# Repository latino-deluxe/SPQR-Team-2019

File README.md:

# SPQR-Team-2019
Official code 2018-2019 SPQR
1st at Romecup2019, Rome
Best Robot Design at Robocup2019, Sydney

#include <E.Latino>

#include <A.Ghezzi>

#include <E.Coletta>

#include <D.Casagrande>

#include <S.Sannino>

#include <G.Treccape>

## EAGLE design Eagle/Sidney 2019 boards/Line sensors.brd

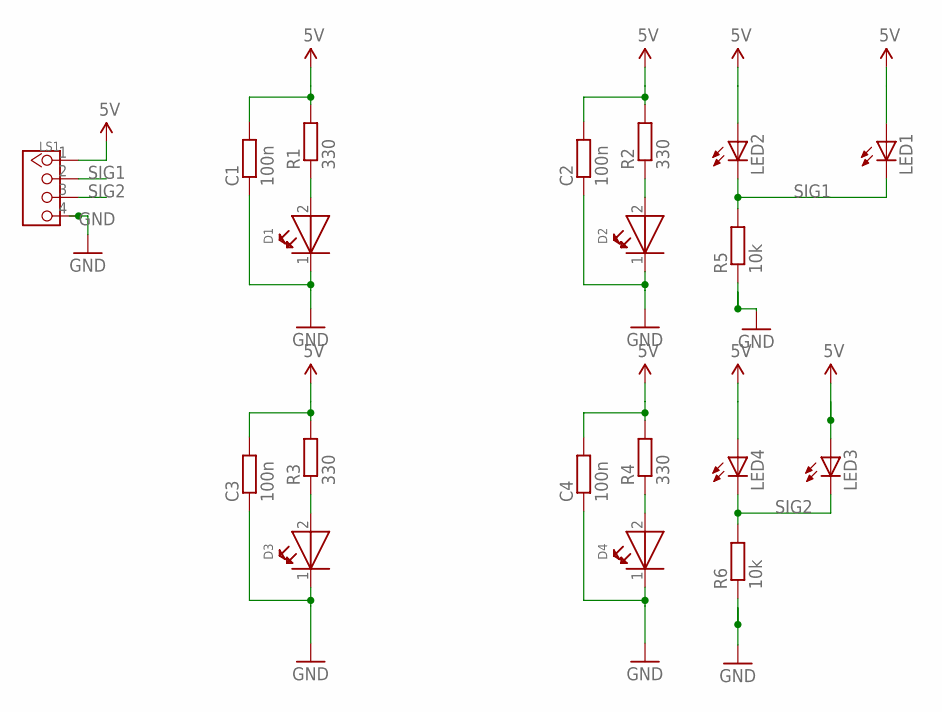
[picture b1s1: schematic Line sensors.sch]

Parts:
C1, C2, C3, C4: 100n; M0805
D1, D2, D3, D4: WL-SMTW-150141AS73100-A; 3528-2PIN
LED1, LED2, LED3, LED4: LED3MM
LS1: TWIG-4P-2.0-2.0; 4P-2.0
R1, R2, R3, R4: 330; M0805
R5, R6: 10k; M0805

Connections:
5V: C1.2, C2.2, C3.2, C4.2, LED1.A, LED2.A, LED3.A, LED4.A, LS1.1, R1.2, R2.2, R3.2, R4.2
GND: C1.1, C2.1, C3.1, C4.1, D1.1 (K), D2.1 (K), D3.1 (K), D4.1 (K), LS1.4, R5.1, R6.1
unnamed: D1.2 (A), R1.1
unnamed: D2.2 (A), R2.1
unnamed: D3.2 (A), R3.1
unnamed: D4.2 (A), R4.1
SIG1: LED1.K (C), LED2.K (C), LS1.2, R5.2
SIG2: LED3.K (C), LED4.K (C), LS1.3, R6.2

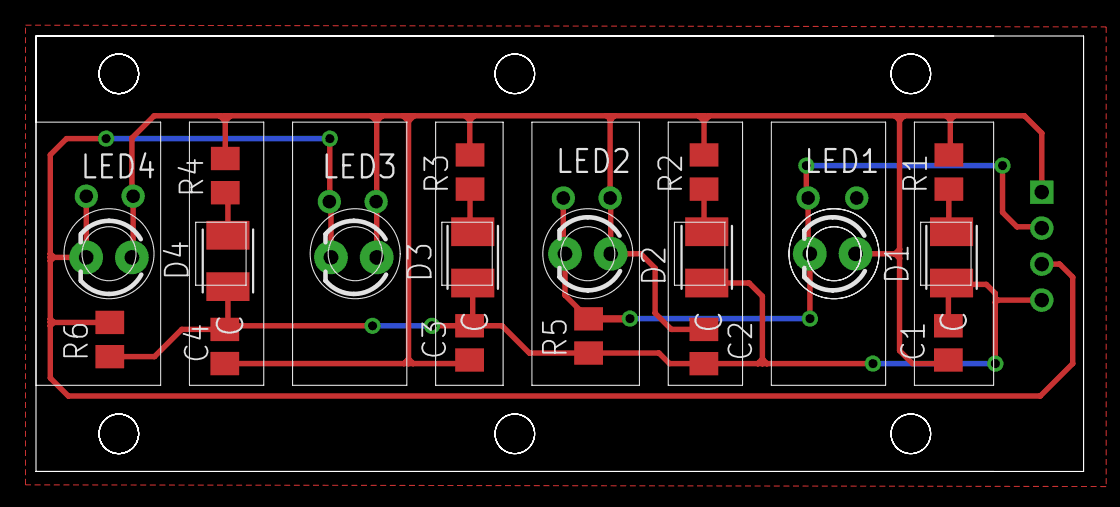
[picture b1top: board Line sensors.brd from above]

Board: 2 copper layers, 58.2 x 24.2 mm, 19 parts (1 on the bottom side), 8 nets.

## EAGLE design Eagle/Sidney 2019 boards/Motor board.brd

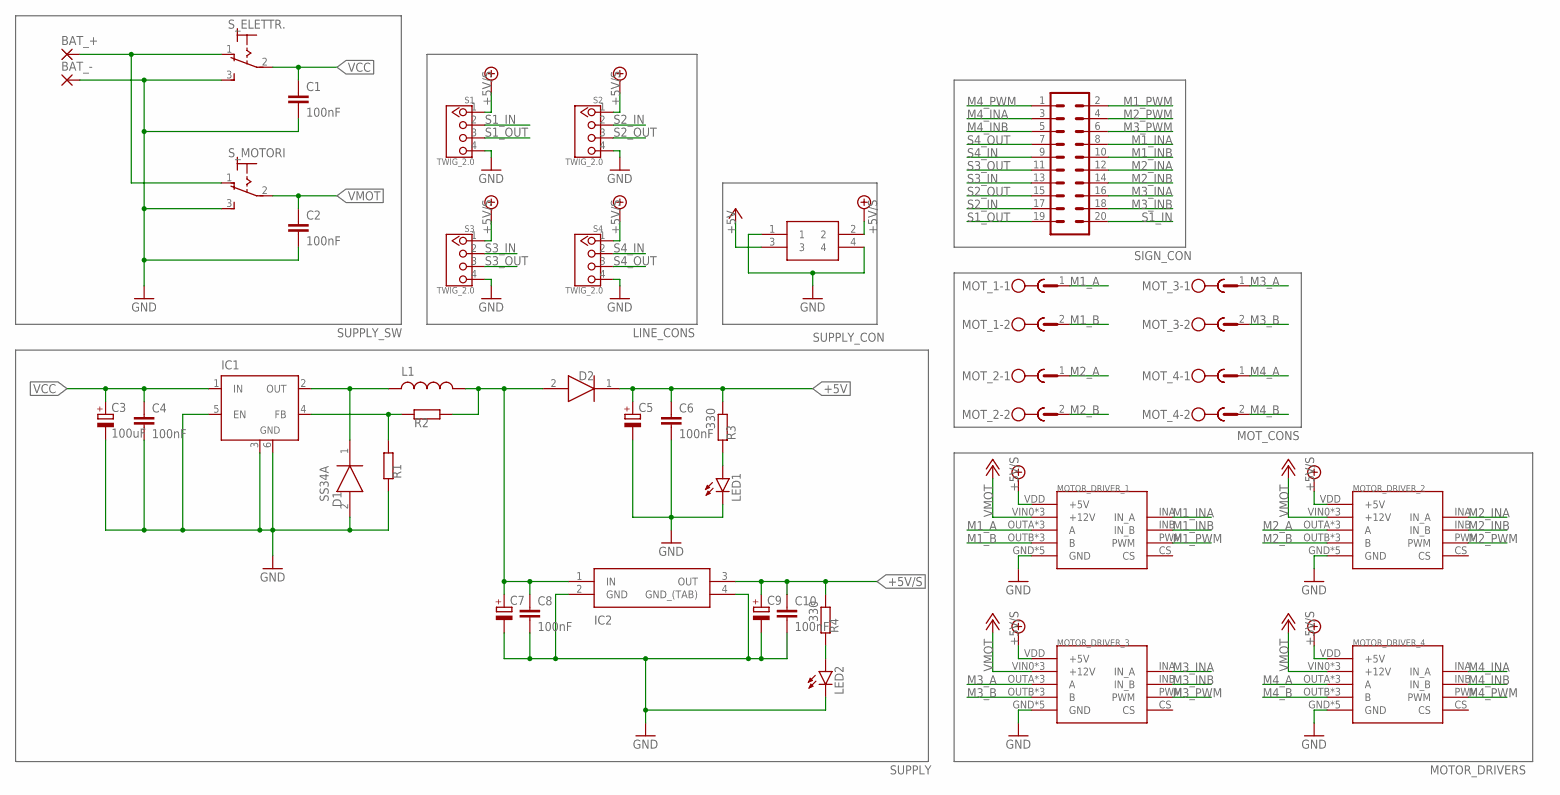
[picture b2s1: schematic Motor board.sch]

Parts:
BAT_+: 3,81/1,4
BAT_-: 3,81/1,4
C1, C2, C4, C6, C8, C10: 100nF; C1206
C3: 100uF; CT7343
C5, C7, C9: CPOL-EUE; PANASONIC_E
D1: SS34A; DIOM5026X262N
D2: SE20FG-M3_H; SODFL3718X108N
IC1: LM2596S; TO263-5
IC2: LM2940CS-5.0_NOPB; TO254P1435X464-4N
L1: 47uH; MSS1260
LED1, LED2: LEDSML1206; SML1206
MOTOR_DRIVER_1, MOTOR_DRIVER_2, MOTOR_DRIVER_3, MOTOR_DRIVER_4: VNH5019
MOT_1, MOT_2, MOT_3, MOT_4: MST2V; MSTBV2
R1, R3, R4: 330; R1206
R2: 1,2k; R1206
S1, S2, S3, S4: TWIG_2.0; 2.0_1X4
SIGN_CON: 20V
SUPPLY_CON: 39-28-1043
S_ELETTR.: 320-916
S_MOTORI: 320-916

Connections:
5.7V-DIRAMAZIONE2: C7.+, C8.1, D2.2 (A), IC2.1 (IN), L1.P$1, R2.1
+5V: C5.+, C6.1, D2.1 (K), R3.1, SUPPLY_CON.3; also elsewhere on the board
GND: BAT_-.1, C1.2, C2.2, C3.-, C4.2, C5.-, C6.2, C7.-, C8.2, C9.-, C10.2, D1.2 (A), IC1.3 (GND), IC1.5 (EN), IC1.6 (GND), IC2.2 (GND), IC2.4 (GND_(TAB)), LED1.C, LED2.C, MOTOR_DRIVER_1.GND, MOTOR_DRIVER_1.GND0 (GND), MOTOR_DRIVER_1.GND1 (GND), MOTOR_DRIVER_1.GND2 (GND), MOTOR_DRIVER_1.GND3 (GND), MOTOR_DRIVER_2.GND, MOTOR_DRIVER_2.GND0 (GND), MOTOR_DRIVER_2.GND1 (GND), MOTOR_DRIVER_2.GND2 (GND), MOTOR_DRIVER_2.GND3 (GND), MOTOR_DRIVER_3.GND, MOTOR_DRIVER_3.GND0 (GND), MOTOR_DRIVER_3.GND1 (GND), MOTOR_DRIVER_3.GND2 (GND), MOTOR_DRIVER_3.GND3 (GND), MOTOR_DRIVER_4.GND, MOTOR_DRIVER_4.GND0 (GND), MOTOR_DRIVER_4.GND1 (GND), MOTOR_DRIVER_4.GND2 (GND), MOTOR_DRIVER_4.GND3 (GND), R1.1, S1.4, S2.4, S3.4, S4.4, SUPPLY_CON.1, SUPPLY_CON.4, S_ELETTR..3 (S), S_MOTORI.3 (S); also elsewhere on the board
M1_A: MOTOR_DRIVER_1.OUTA (A), MOTOR_DRIVER_1.OUTA2 (A), MOTOR_DRIVER_1.OUTA3 (A), MOT_1.1
M1_B: MOTOR_DRIVER_1.OUTB (B), MOTOR_DRIVER_1.OUTB1 (B), MOTOR_DRIVER_1.OUTB3 (B), MOT_1.2
M1_INA: MOTOR_DRIVER_1.INA (IN_A), SIGN_CON.8
M1_INB: MOTOR_DRIVER_1.INB (IN_B), SIGN_CON.10
M1_PWM: MOTOR_DRIVER_1.PWM, SIGN_CON.2
M2_A: MOTOR_DRIVER_2.OUTA (A), MOTOR_DRIVER_2.OUTA2 (A), MOTOR_DRIVER_2.OUTA3 (A), MOT_2.1
M2_B: MOTOR_DRIVER_2.OUTB (B), MOTOR_DRIVER_2.OUTB1 (B), MOTOR_DRIVER_2.OUTB3 (B), MOT_2.2
M2_INA: MOTOR_DRIVER_2.INA (IN_A), SIGN_CON.12
M2_INB: MOTOR_DRIVER_2.INB (IN_B), SIGN_CON.14
M2_PWM: MOTOR_DRIVER_2.PWM, SIGN_CON.4
M3_A: MOTOR_DRIVER_3.OUTA (A), MOTOR_DRIVER_3.OUTA2 (A), MOTOR_DRIVER_3.OUTA3 (A), MOT_3.1
M3_B: MOTOR_DRIVER_3.OUTB (B), MOTOR_DRIVER_3.OUTB1 (B), MOTOR_DRIVER_3.OUTB3 (B), MOT_3.2
M3_INA: MOTOR_DRIVER_3.INA (IN_A), SIGN_CON.16
M3_INB: MOTOR_DRIVER_3.INB (IN_B), SIGN_CON.18
M3_PWM: MOTOR_DRIVER_3.PWM, SIGN_CON.6
M4_A: MOTOR_DRIVER_4.OUTA (A), MOTOR_DRIVER_4.OUTA2 (A), MOTOR_DRIVER_4.OUTA3 (A), MOT_4.1
M4_B: MOTOR_DRIVER_4.OUTB (B), MOTOR_DRIVER_4.OUTB1 (B), MOTOR_DRIVER_4.OUTB3 (B), MOT_4.2
M4_INA: MOTOR_DRIVER_4.INA (IN_A), SIGN_CON.3
M4_INB: MOTOR_DRIVER_4.INB (IN_B), SIGN_CON.5
M4_PWM: MOTOR_DRIVER_4.PWM, SIGN_CON.1
unnamed: BAT_+.1, S_ELETTR..1 (O), S_MOTORI.1 (O)
unnamed: LED2.A, R4.2
unnamed: LED1.A, R3.2
unnamed: D1.1 (K), IC1.2 (OUT), L1.P$2
unnamed: IC1.4 (FB), R1.2, R2.2
S1_IN: S1.2, SIGN_CON.20
S1_OUT: S1.3, SIGN_CON.19
S2_IN: S2.2, SIGN_CON.17
S2_OUT: S2.3, SIGN_CON.15
S3_IN: S3.2, SIGN_CON.13
S3_OUT: S3.3, SIGN_CON.11
S4_IN: S4.2, SIGN_CON.9
S4_OUT: S4.3, SIGN_CON.7
VCC: C1.1, C3.+, C4.1, IC1.1 (IN), S_ELETTR..2
VMOT: C2.1, MOTOR_DRIVER_1.VIN0 (+12V), MOTOR_DRIVER_1.VIN1 (+12V), MOTOR_DRIVER_1.VIN2 (+12V), MOTOR_DRIVER_2.VIN0 (+12V), MOTOR_DRIVER_2.VIN1 (+12V), MOTOR_DRIVER_2.VIN2 (+12V), MOTOR_DRIVER_3.VIN0 (+12V), MOTOR_DRIVER_3.VIN1 (+12V), MOTOR_DRIVER_3.VIN2 (+12V), MOTOR_DRIVER_4.VIN0 (+12V), MOTOR_DRIVER_4.VIN1 (+12V), MOTOR_DRIVER_4.VIN2 (+12V), S_MOTORI.2

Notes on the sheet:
SUPPLY_SW
SUPPLY
LINE_CONS
MOT_CONS
MOTOR_DRIVERS

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
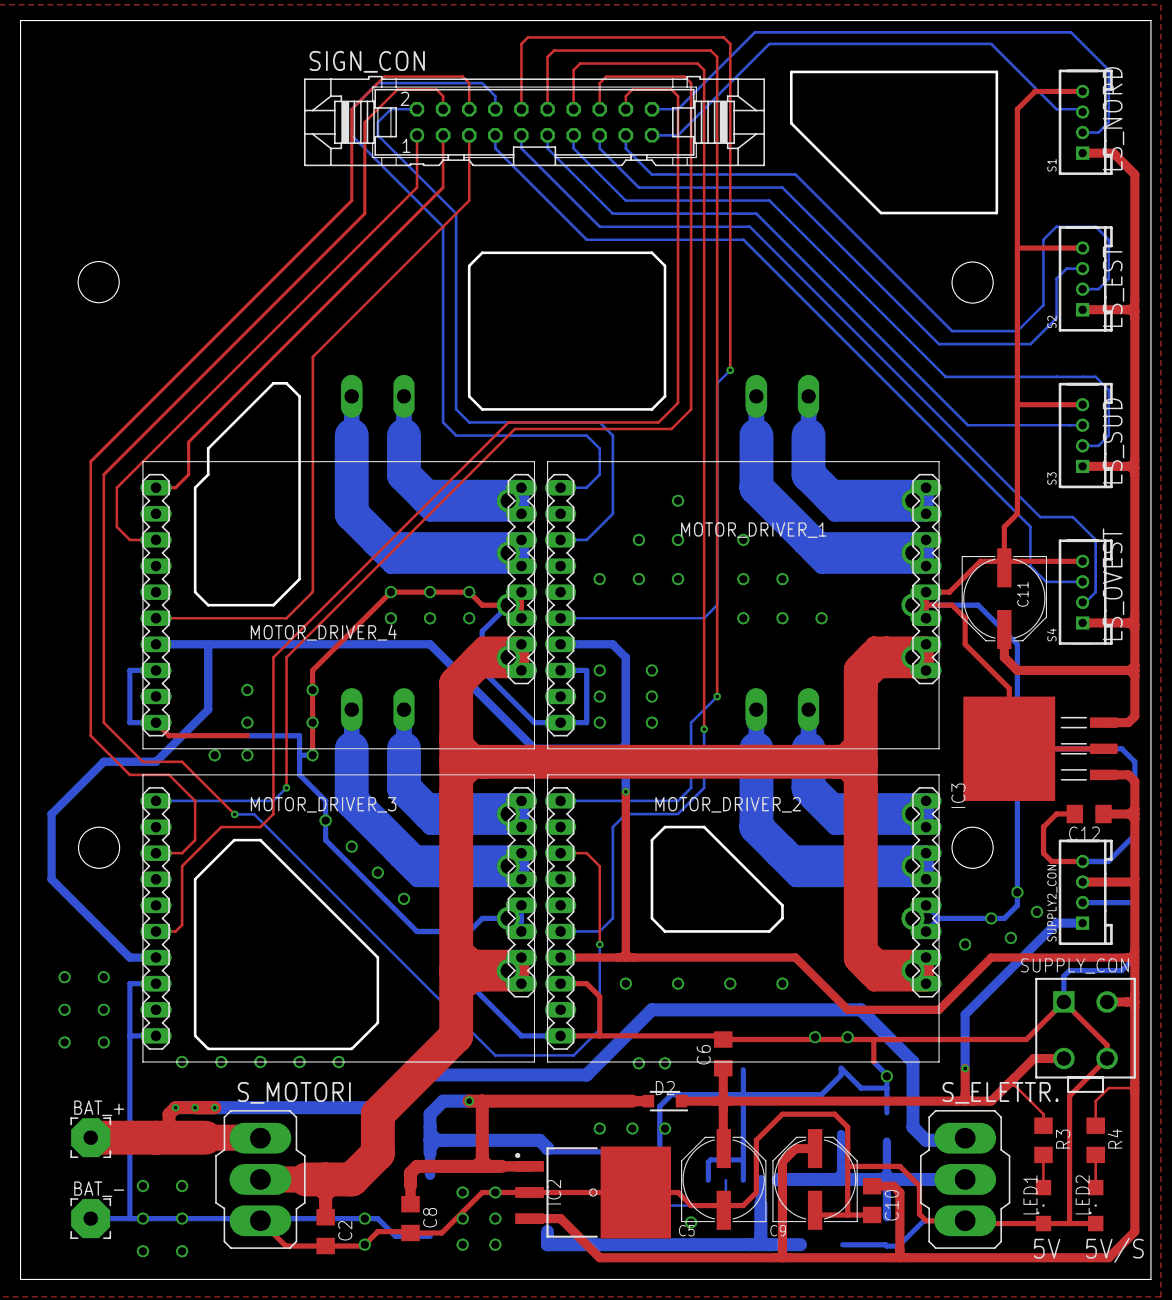
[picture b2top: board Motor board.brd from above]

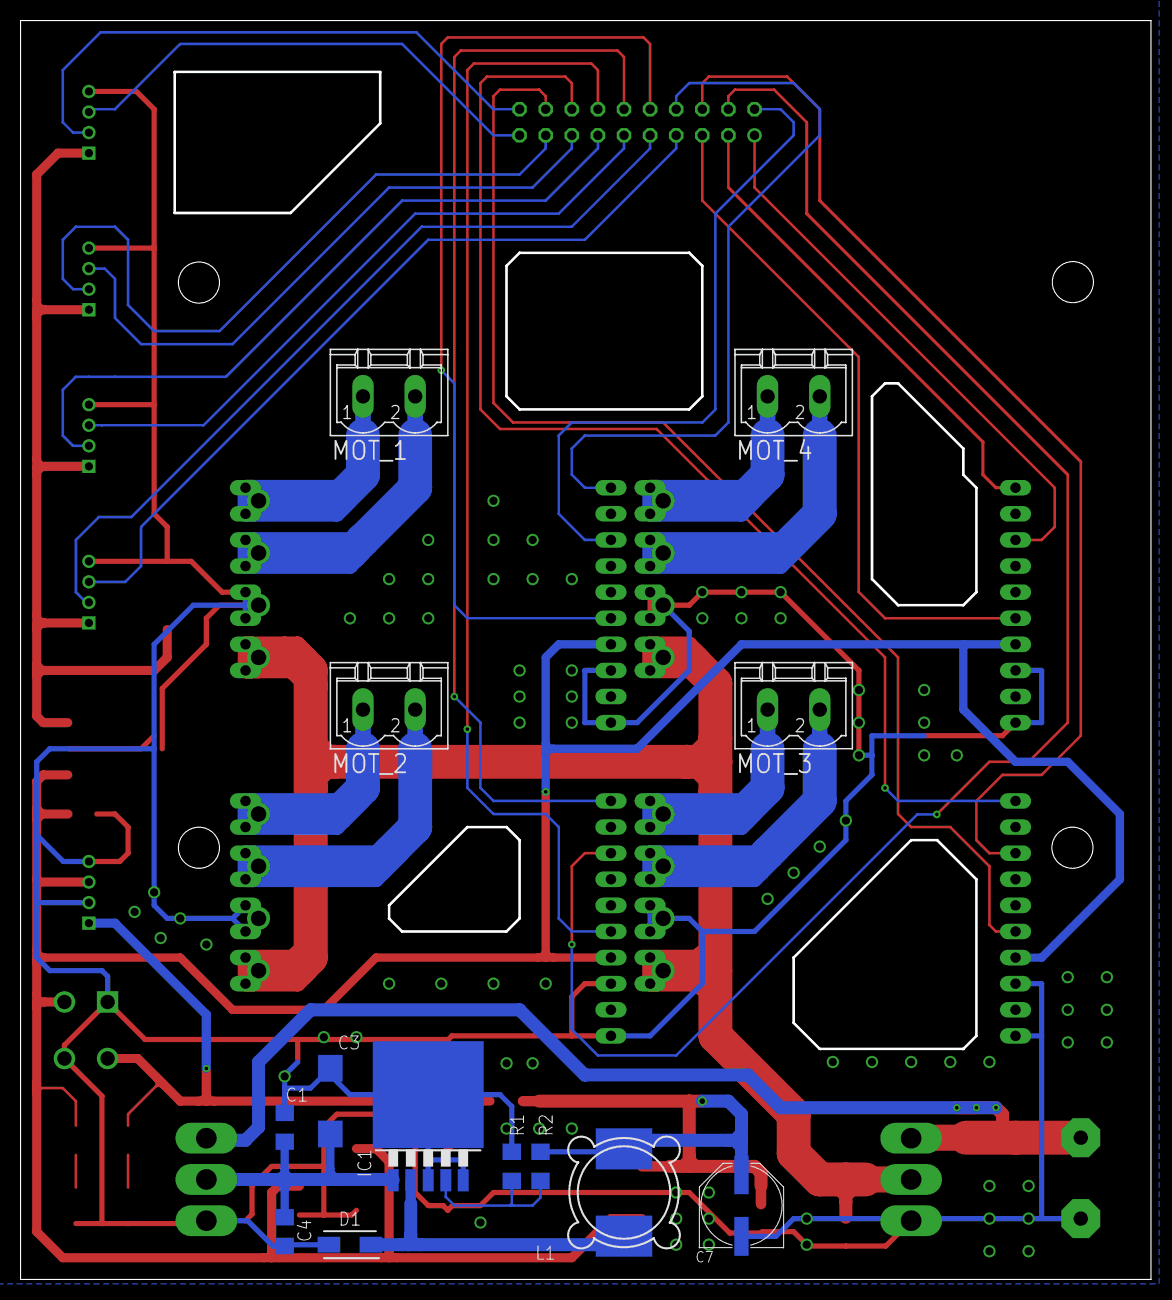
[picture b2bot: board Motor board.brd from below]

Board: 2 copper layers, 110.0 x 122.5 mm, 43 parts (13 on the bottom side), 40 nets.

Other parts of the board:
C11: PANASONIC_E
C12: 100nF; C1206
IC3: LM3940IS-3.3; TO254P1435X457-4N
SUPPLY2_CON: TWIG_2.0; 2.0_1X4

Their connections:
+5V: SUPPLY2_CON.1; also elsewhere on the board
GND: C11.-, C12.2, IC3.2, IC3.4, SUPPLY2_CON.2, SUPPLY2_CON.4; also elsewhere on the board

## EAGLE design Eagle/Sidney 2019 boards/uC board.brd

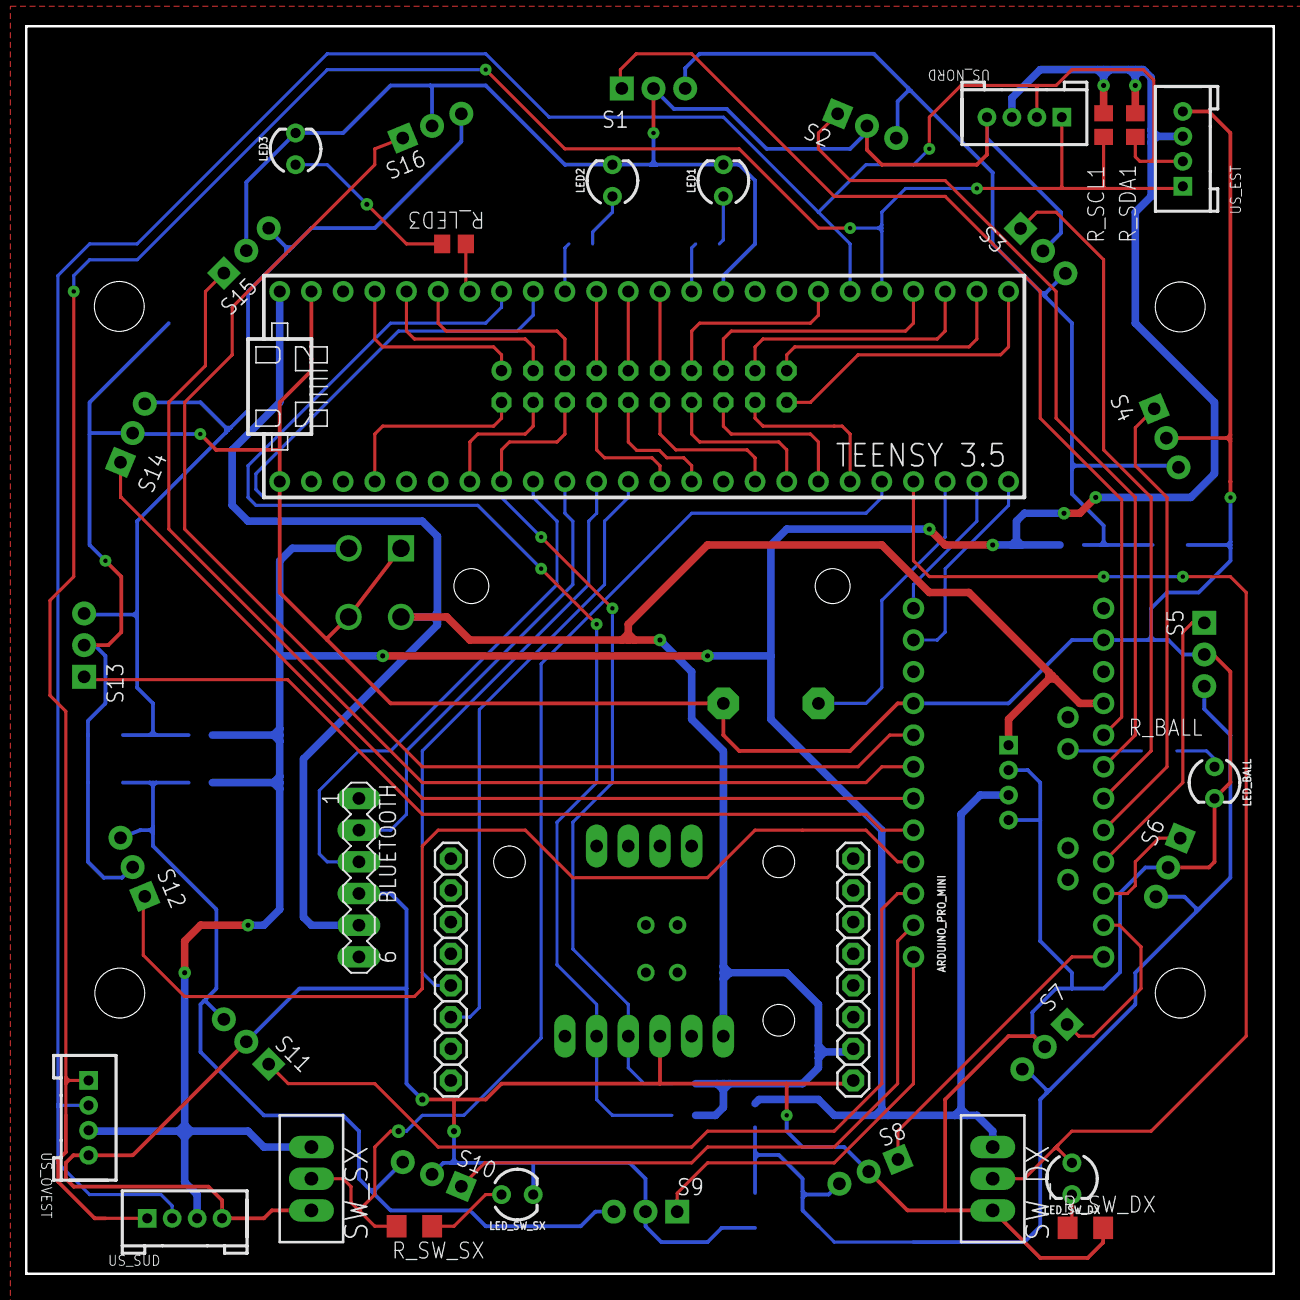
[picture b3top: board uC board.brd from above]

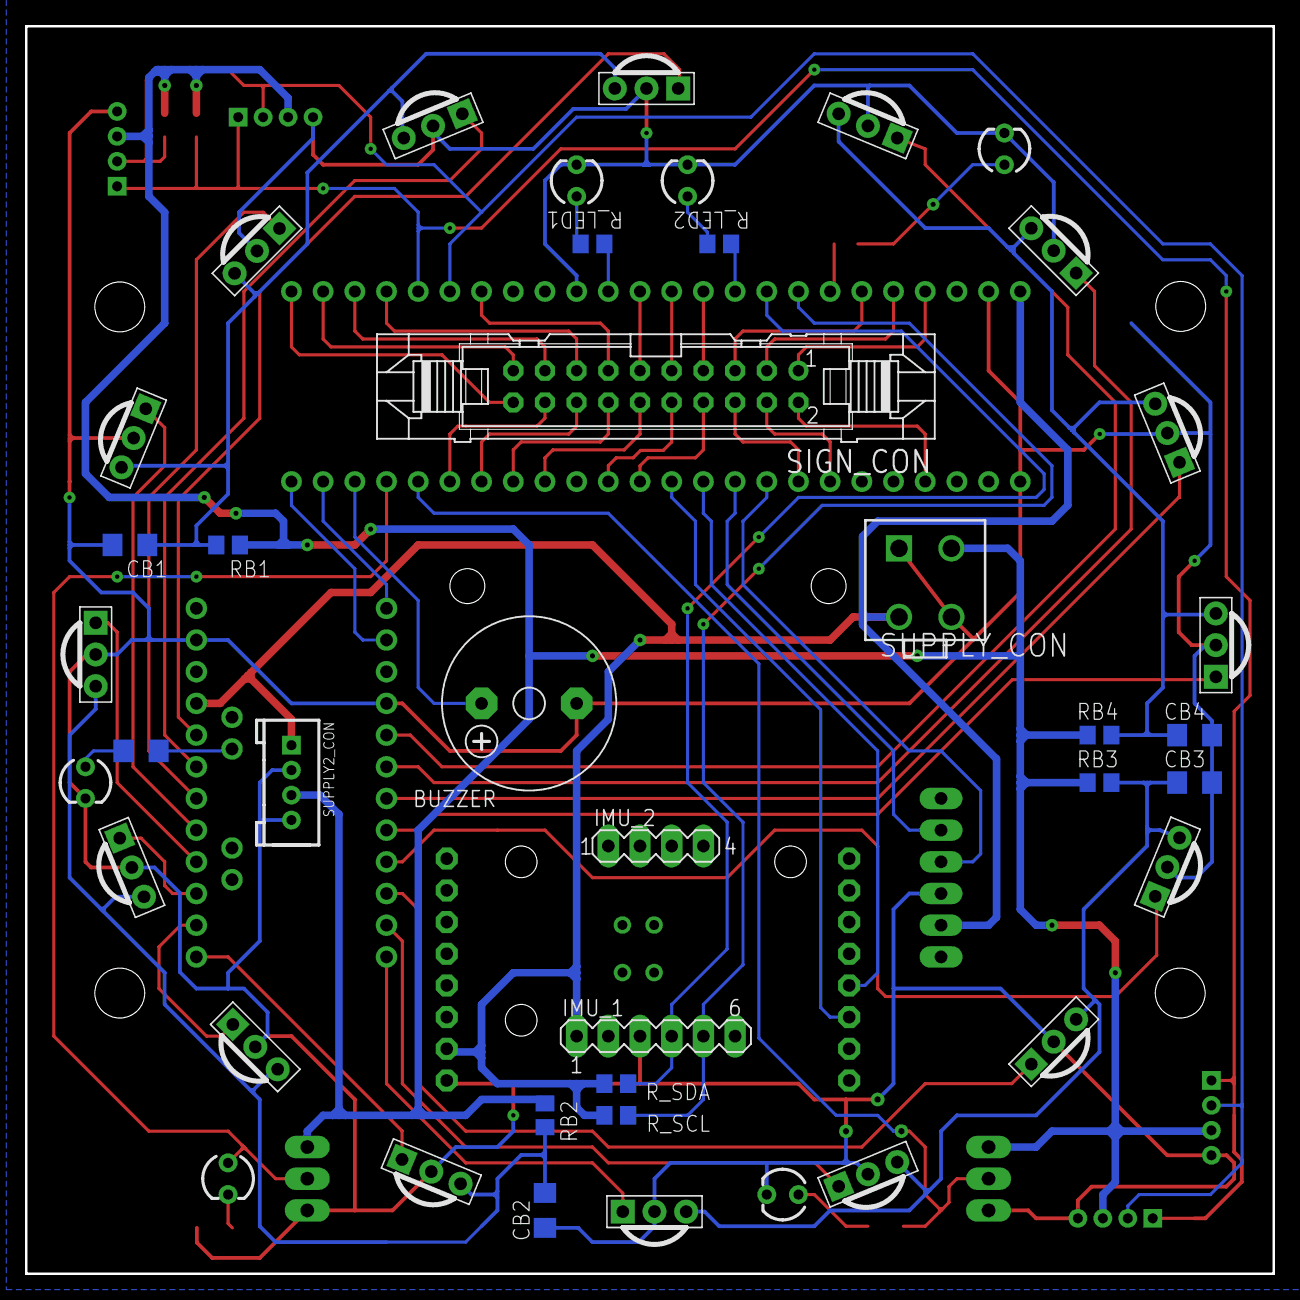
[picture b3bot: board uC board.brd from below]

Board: 2 copper layers, 100.0 x 100.0 mm, 56 parts (35 on the bottom side), 66 nets.

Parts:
ARDUINO_PRO_MINI: ARDUINO_PRO_MINI
BLUETOOTH: MA06-1
BUZZER: F/CM12P
CB1, CB2, CB3, CB4: 0.1uF; C1206
IMU_1: MA06-1
IMU_2: MA04-1
J1: 39-28-1043
LED1, LED2, LED3: LED_3MM
LED_BALL: LED_3MM
LED_SW_DX: LED_3MM
LED_SW_SX: LED_3MM
RB1, RB2, RB3, RB4: 33; R0805
R_BALL: 330; R1206
R_LED1, R_LED2, R_LED3: 68/75; R0805
R_SCL, R_SCL1: 3.3k; R0805
R_SDA, R_SDA1: 3.3k; R0805
R_SW_DX: 330; R1206
R_SW_SX: 330; R1206
S1, S2, S3, S4, S5, S6, S7, S8, S9, S10, S11, S12, S13, S14, S15, S16: PNA460XM
SIGN_CON: 20V
SUPPLY2_CON: TWIG_2.0; 2.0_1X4
SW_DX: TL38PO; TL3XPO
SW_SX: TL38PO; TL3XPO
TEENSY_3.5: TEENSY_3.5/3.6
U$2: OPENMV3
US_EST: TWIG_2.0; 2.0_1X4
US_NORD: TWIG_2.0; 2.0_1X4
US_OVEST: TWIG_2.0; 2.0_1X4
US_SUD: TWIG_2.0; 2.0_1X4

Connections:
+5V: ARDUINO_PRO_MINI.21, BLUETOOTH.5, IMU_1.1, J1.3, R_SCL.2, R_SDA.2, SUPPLY2_CON.1, TEENSY_3.5.VIN, U$2.27
+5V/S: J1.2, RB1.1, RB2.1, RB3.1, RB4.1, R_SCL1.2, R_SDA1.2, SUPPLY2_CON.3, SW_DX.1, SW_SX.1, US_EST.3, US_NORD.3, US_OVEST.3, US_SUD.3
BUZZ: BUZZER.+, TEENSY_3.5.30
GND: ARDUINO_PRO_MINI.4, ARDUINO_PRO_MINI.23, BLUETOOTH.4, BUZZER.-, CB1.2, CB2.2, CB3.2, CB4.2, IMU_1.3, J1.1, J1.4, LED1.K, LED2.K, LED3.K, LED_BALL.K, LED_SW_SX.K, R_SW_DX.1, S1.2, S2.2, S3.2, S4.2, S5.2, S6.2, S7.2, S8.2, S9.2, S10.2, S11.2, S12.2, S13.2, S14.2, S15.2, S16.2, SUPPLY2_CON.2, SUPPLY2_CON.4, SW_DX.3, SW_SX.3, TEENSY_3.5.AGND, TEENSY_3.5.GND, TEENSY_3.5.GND2, U$2.28, US_EST.4, US_NORD.4, US_OVEST.4, US_SUD.4
M1_INA: SIGN_CON.8, TEENSY_3.5.11/MOSI
M1_INB: SIGN_CON.10, TEENSY_3.5.12/MISO
M1_PWM: SIGN_CON.2, TEENSY_3.5.2
M2_INA: SIGN_CON.12, TEENSY_3.5.24
M2_INB: SIGN_CON.14, TEENSY_3.5.25
M2_PWM: SIGN_CON.4, TEENSY_3.5.5
M3_INA: SIGN_CON.16, TEENSY_3.5.26
M3_INB: SIGN_CON.18, TEENSY_3.5.27
M3_PWM: SIGN_CON.6, TEENSY_3.5.6
M4_INA: SIGN_CON.3, TEENSY_3.5.22/A8
M4_INB: SIGN_CON.5, TEENSY_3.5.21/A7
M4_PWM: SIGN_CON.1, TEENSY_3.5.23/A9
unnamed: R_LED1.1, TEENSY_3.5.13/SCK
unnamed: LED1.A, R_LED1.2
unnamed: LED_BALL.A, R_BALL.1
unnamed: ARDUINO_PRO_MINI.A4, R_BALL.2
unnamed: LED_SW_SX.A, R_SW_SX.1
unnamed: LED2.A, R_LED2.2
unnamed: LED3.A, R_LED3.2
unnamed: R_LED3.1, TEENSY_3.5.20/A6
unnamed: LED_SW_DX.K, R_SW_DX.2
unnamed: R_LED2.1, TEENSY_3.5.17/A3
POWER_BLOK_1: CB2.1, RB2.2, S5.3, S6.3, S7.3, S8.3
POWER_BLOK_2: CB1.1, RB1.2, S1.3, S2.3, S3.3, S4.3
POWER_BLOK_3: CB3.1, RB3.2, S9.3, S10.3, S11.3, S12.3
POWER_BLOK_4: CB4.1, RB4.2, S13.3, S14.3, S15.3, S16.3
RX2: TEENSY_3.5.9/CS, U$2.15
RX3: BLUETOOTH.3, TEENSY_3.5.7
RX4: ARDUINO_PRO_MINI.1, TEENSY_3.5.31/A12
S1_IN: SIGN_CON.20, TEENSY_3.5.33/A14
S1_OUT: SIGN_CON.19, TEENSY_3.5.34/A15
S2_IN: SIGN_CON.17, TEENSY_3.5.35/A16
S2_OUT: SIGN_CON.15, TEENSY_3.5.36/A17
S3_IN: SIGN_CON.13, TEENSY_3.5.39/A20
S3_OUT: SIGN_CON.11, TEENSY_3.5.14/A0
S4_IN: SIGN_CON.9, TEENSY_3.5.15/A1
S4_OUT: SIGN_CON.7, TEENSY_3.5.16/A2
SCL1: R_SCL1.1, TEENSY_3.5.37/A18, US_EST.1, US_NORD.1, US_OVEST.1, US_SUD.1
SCL_I2C: IMU_1.5, R_SCL.1, TEENSY_3.5.19/A5/SCL
SDA1: R_SDA1.1, TEENSY_3.5.38/A19, US_EST.2, US_NORD.2, US_OVEST.2, US_SUD.2
SDA_I2C: IMU_1.4, R_SDA.1, TEENSY_3.5.18/A4/SDA
SP1: ARDUINO_PRO_MINI.20, S1.1
SP2: ARDUINO_PRO_MINI.19, S2.1
SP3: ARDUINO_PRO_MINI.18, S3.1
SP4: ARDUINO_PRO_MINI.17, S4.1
SP5: ARDUINO_PRO_MINI.16, S5.1
SP6: ARDUINO_PRO_MINI.15, S6.1
SP7: ARDUINO_PRO_MINI.14, S7.1
SP8: ARDUINO_PRO_MINI.13, S8.1
SP9: ARDUINO_PRO_MINI.12, S9.1
SP10: ARDUINO_PRO_MINI.11, S10.1
SP11: ARDUINO_PRO_MINI.10, S11.1
SP12: ARDUINO_PRO_MINI.9, S12.1
SP13: ARDUINO_PRO_MINI.8, S13.1
SP14: ARDUINO_PRO_MINI.7, S14.1
SP15: ARDUINO_PRO_MINI.6, S15.1
SP16: ARDUINO_PRO_MINI.5, S16.1
SW_DX: LED_SW_DX.A, SW_DX.2, TEENSY_3.5.29
SW_SX: R_SW_SX.2, SW_SX.2, TEENSY_3.5.28
TX2: TEENSY_3.5.10/CS, U$2.16
TX3: BLUETOOTH.2, TEENSY_3.5.8
TX4: ARDUINO_PRO_MINI.2, TEENSY_3.5.32/A13

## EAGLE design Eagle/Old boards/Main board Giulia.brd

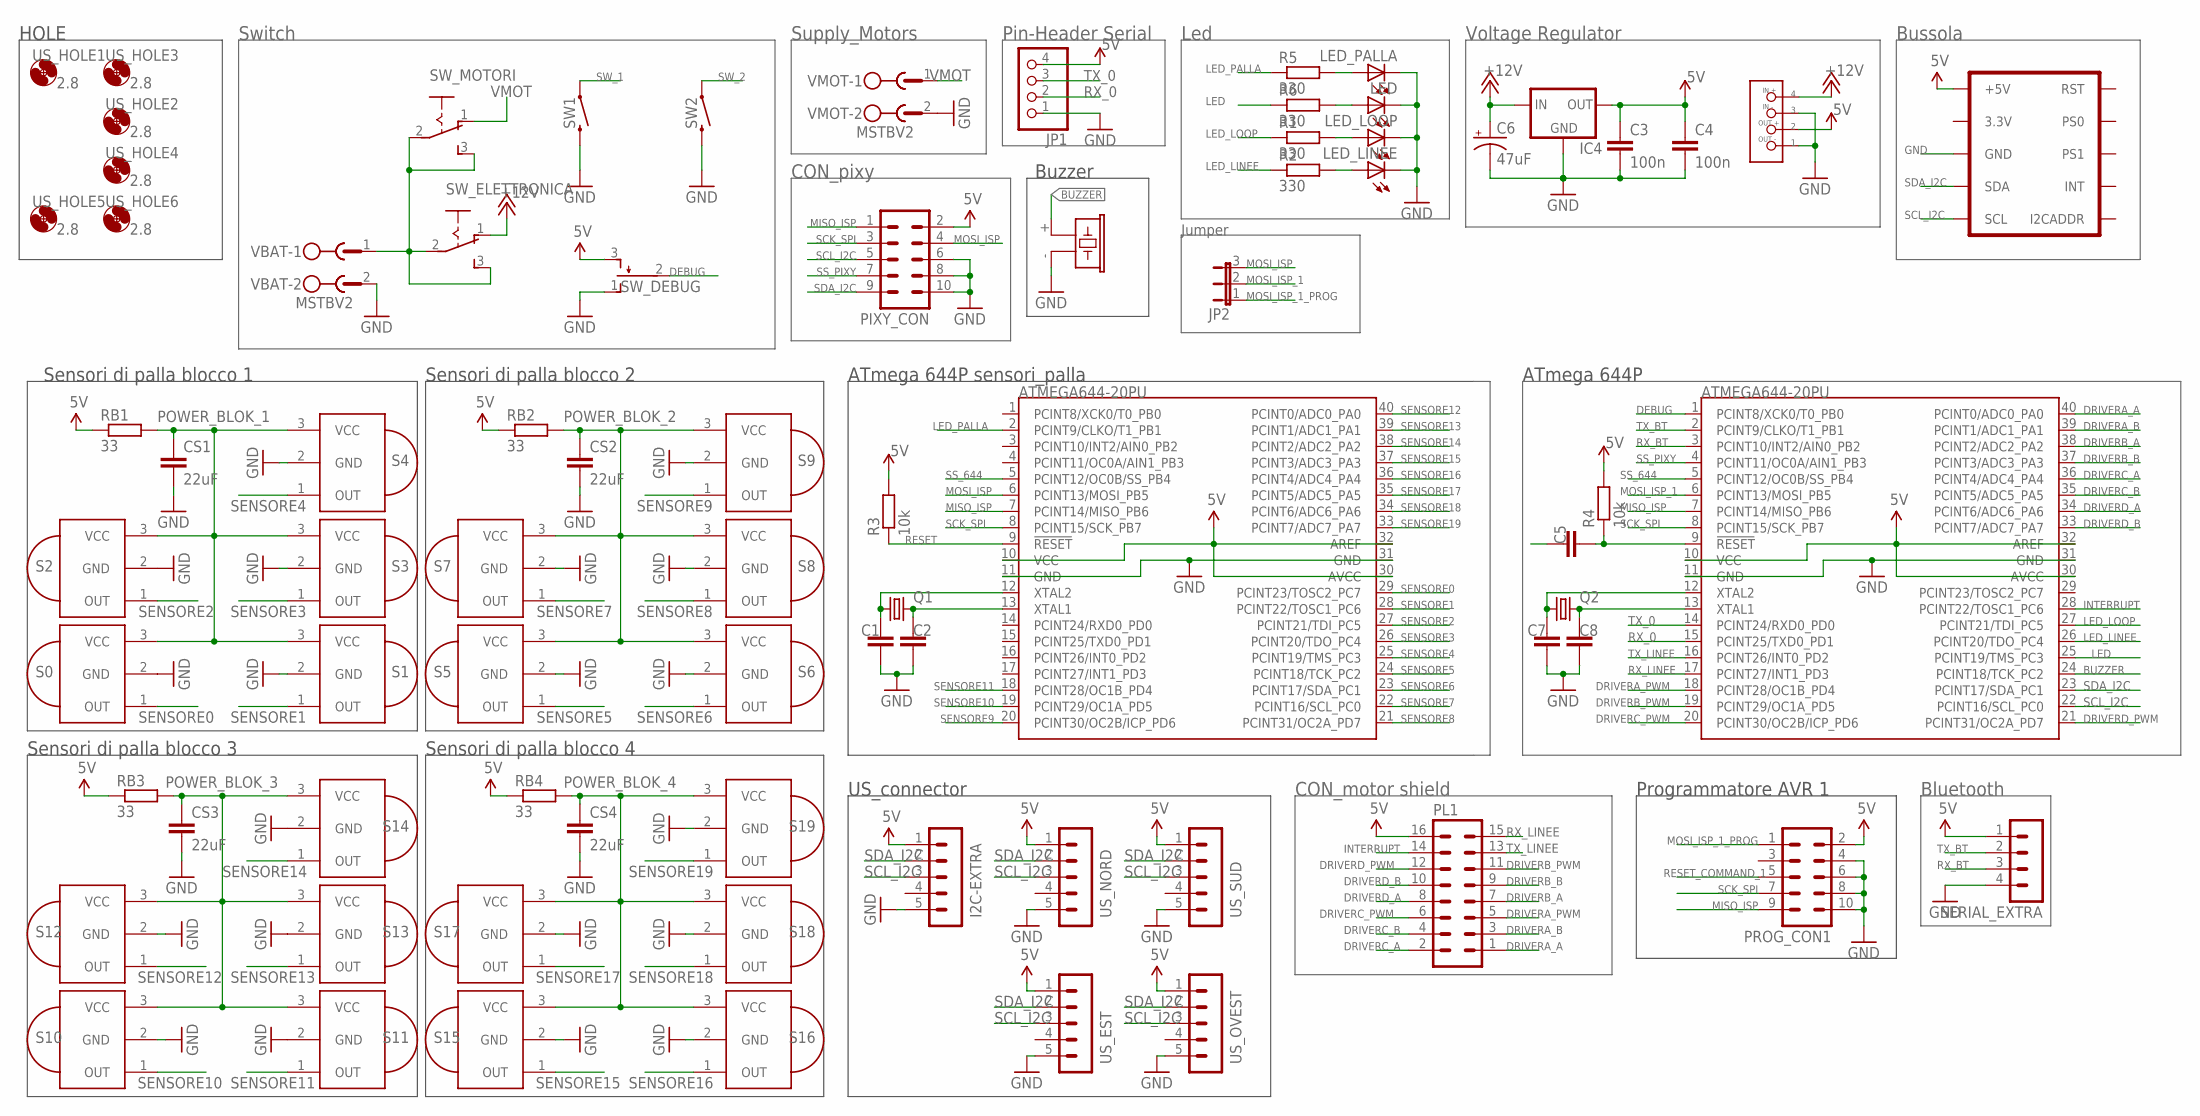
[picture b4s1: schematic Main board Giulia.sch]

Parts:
C1, C2, C7, C8: 18p; C1206
C3, C4: 100n; C050-025X075
C5: 0.1uF; C1206
C6: 47uF; CPOL-RADIAL-100UF-25V
CS1, CS2, CS3, CS4: 22uF; C1206
I2C-EXTRA: MA05-1
IC2, IC3: ATMEGA644-20PU; DIL40
IC4: V_REG_78XXSIDE; 78XXL
JP1: PINHD-1X4; 1X04
JP2: JP2E; JP2
LED: LED3MM
LED_LINEE: LED3MM
LED_LOOP: LED3MM
LED_PALLA: LED3MM
PIXY_CON: 10V
PL1: 16V
PROG_CON1: 10V
Q1, Q2: CRYSTALHC49UV; HC49U-V
R1, R2, R5, R6: 330; M1206
R3, R4: 10k; M1206
RB1, RB2, RB3, RB4: 33; 0207/10
S0, S1, S2, S3, S4, S5, S6, S7, S8, S9, S10, S11, S12, S13, S14, S15, S16, S17, S18, S19: PNA460XM
SERIAL_EXTRA: MA04-1
SG1: F/CM12P
SW1, SW2: SWITCH-MOMENTARY-2; SWITCH_EVQ2
SW_DEBUG: TL38PO; TL3XPO
SW_ELETTRONICA: 255SB
SW_MOTORI: 255SB
U$1: MINI3ADCDCLM2596; MINI3ADCDCLM2595
U$17: BNO055
US_EST: MA05-1
US_HOLE1, US_HOLE2, US_HOLE3, US_HOLE4, US_HOLE5, US_HOLE6: 2.8; 2,8
US_NORD: MA05-1
US_OVEST: MA05-1
US_SUD: MA05-1
VBAT: MSTBV2
VMOT: MSTBV2

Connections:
5V: C3.1, C4.1, I2C-EXTRA.1, IC2.10 (VCC), IC2.30 (AVCC), IC2.32 (AREF), IC3.10 (VCC), IC3.30 (AVCC), IC3.32 (AREF), IC4.OUT, JP1.4, PIXY_CON.2, PL1.16, PROG_CON1.2, R3.2, R4.2, RB1.1, RB2.1, RB3.1, RB4.1, SERIAL_EXTRA.1, SW_DEBUG.3 (S), U$1.P$1 (OUT+), U$1.P$8 (OUT+), U$17.VIN (+5V), US_EST.1, US_NORD.1, US_OVEST.1, US_SUD.1
+12V: C6.1 (+), IC4.IN, SW_ELETTRONICA.1 (O), U$1.P$2 (IN1), U$1.P$7 (IN1)
BUZZER: IC3.24 (PCINT18/TCK_PC2), SG1.+ (1)
DEBUG: IC3.1 (PCINT8/XCK0/T0_PB0), SW_DEBUG.2
DRIVERA_A: IC3.40 (PCINT0/ADC0_PA0), PL1.1
DRIVERA_B: IC3.39 (PCINT1/ADC1_PA1), PL1.3
DRIVERA_PWM: IC3.18 (PCINT28/OC1B_PD4), PL1.5
DRIVERB_A: IC3.38 (PCINT2/ADC2_PA2), PL1.7
DRIVERB_B: IC3.37 (PCINT3/ADC3_PA3), PL1.9
DRIVERB_PWM: IC3.19 (PCINT29/OC1A_PD5), PL1.11
DRIVERC_A: IC3.36 (PCINT4/ADC4_PA4), PL1.2
DRIVERC_B: IC3.35 (PCINT5/ADC5_PA5), PL1.4
DRIVERC_PWM: IC3.20 (PCINT30/OC2B/ICP_PD6), PL1.6
DRIVERD_A: IC3.34 (PCINT6/ADC6_PA6), PL1.8
DRIVERD_B: IC3.33 (PCINT7/ADC7_PA7), PL1.10
DRIVERD_PWM: IC3.21 (PCINT31/OC2A_PD7), PL1.12
GND: C1.2, C2.2, C3.2, C4.2, C6.2 (-), C7.2, C8.2, CS1.2, CS2.2, CS3.2, CS4.2, I2C-EXTRA.5, IC2.11 (GND), IC2.31 (GND), IC3.11 (GND), IC3.31 (GND), IC4.GND, JP1.1, LED.K (C), LED_LINEE.K (C), LED_LOOP.K (C), LED_PALLA.K (C), PIXY_CON.6, PIXY_CON.8, PIXY_CON.10, PROG_CON1.4, PROG_CON1.6, PROG_CON1.8, PROG_CON1.10, S0.2 (GND), S1.2 (GND), S2.2 (GND), S3.2 (GND), S4.2 (GND), S5.2 (GND), S6.2 (GND), S7.2 (GND), S8.2 (GND), S9.2 (GND), S10.2 (GND), S11.2 (GND), S12.2 (GND), S13.2 (GND), S14.2 (GND), S15.2 (GND), S16.2 (GND), S17.2 (GND), S18.2 (GND), S19.2 (GND), SERIAL_EXTRA.4, SG1.- (2), SW1.P$2 (2), SW2.P$2 (2), SW_DEBUG.1 (O), U$1.P$3 (IN2), U$1.P$4 (OUT-), U$1.P$5 (IN2), U$1.P$6 (OUT-), U$17.GND, US_EST.5, US_NORD.5, US_OVEST.5, US_SUD.5, VBAT.2, VMOT.2
INTERRUPT: IC3.28 (PCINT22/TOSC1_PC6), PL1.14
LED: IC3.25 (PCINT19/TMS_PC3), R6.1
LED_LINEE: IC3.26 (PCINT20/TDO_PC4), R2.1
LED_LOOP: IC3.27 (PCINT21/TDI_PC5), R1.1
LED_PALLA: IC2.2 (PCINT9/CLKO/T1_PB1), R5.1
MISO_ISP: IC2.7 (PCINT14/MISO_PB6), IC3.7 (PCINT14/MISO_PB6), PIXY_CON.1, PROG_CON1.9
MOSI_ISP: IC2.6 (PCINT13/MOSI_PB5), JP2.3, PIXY_CON.4
MOSI_ISP_1: IC3.6 (PCINT13/MOSI_PB5), JP2.2
MOSI_ISP_1_PROG: JP2.1, PROG_CON1.1
unnamed: C1.1, IC2.12 (XTAL2), Q1.1
unnamed: C2.1, IC2.13 (XTAL1), Q1.2
unnamed: LED.A, R6.2
unnamed: LED_LOOP.A, R1.2
unnamed: SW_ELETTRONICA.2, SW_ELETTRONICA.3 (S), SW_MOTORI.2, SW_MOTORI.3 (S), VBAT.1
unnamed: C7.1, IC3.12 (XTAL2), Q2.1
unnamed: C8.1, IC3.13 (XTAL1), Q2.2
unnamed: LED_PALLA.A, R5.2
unnamed: LED_LINEE.A, R2.2
unnamed: C5.2, IC3.9 (!RESET), R4.1
POWER_BLOK_1: CS1.1, RB1.2, S0.3 (VCC), S1.3 (VCC), S2.3 (VCC), S3.3 (VCC), S4.3 (VCC)
POWER_BLOK_2: CS2.1, RB2.2, S5.3 (VCC), S6.3 (VCC), S7.3 (VCC), S8.3 (VCC), S9.3 (VCC)
POWER_BLOK_3: CS3.1, RB3.2, S10.3 (VCC), S11.3 (VCC), S12.3 (VCC), S13.3 (VCC), S14.3 (VCC)
POWER_BLOK_4: CS4.1, RB4.2, S15.3 (VCC), S16.3 (VCC), S17.3 (VCC), S18.3 (VCC), S19.3 (VCC)
RESET: IC2.9 (!RESET), R3.1
RESET_COMMAND_1: C5.1, PROG_CON1.5
RX_0: IC3.15 (PCINT25/TXD0_PD1), JP1.2
RX_BT: IC3.3 (PCINT10/INT2/AIN0_PB2), SERIAL_EXTRA.3
RX_LINEE: IC3.17 (PCINT27/INT1_PD3), PL1.15
SCK_SPI: IC2.8 (PCINT15/SCK_PB7), IC3.8 (PCINT15/SCK_PB7), PIXY_CON.3, PROG_CON1.7
SCL_I2C: I2C-EXTRA.3, IC3.22 (PCINT16/SCL_PC0), PIXY_CON.5, U$17.SCL, US_EST.3, US_NORD.3, US_OVEST.3, US_SUD.3
SDA_I2C: I2C-EXTRA.2, IC3.23 (PCINT17/SDA_PC1), PIXY_CON.9, U$17.SDA, US_EST.2, US_NORD.2, US_OVEST.2, US_SUD.2
SENSORE0: IC2.29 (PCINT23/TOSC2_PC7), S0.1 (OUT)
SENSORE1: IC2.28 (PCINT22/TOSC1_PC6), S1.1 (OUT)
SENSORE2: IC2.27 (PCINT21/TDI_PC5), S2.1 (OUT)
SENSORE3: IC2.26 (PCINT20/TDO_PC4), S3.1 (OUT)
SENSORE4: IC2.25 (PCINT19/TMS_PC3), S4.1 (OUT)
SENSORE5: IC2.24 (PCINT18/TCK_PC2), S5.1 (OUT)
SENSORE6: IC2.23 (PCINT17/SDA_PC1), S6.1 (OUT)
SENSORE7: IC2.22 (PCINT16/SCL_PC0), S7.1 (OUT)
SENSORE8: IC2.21 (PCINT31/OC2A_PD7), S8.1 (OUT)
SENSORE9: IC2.20 (PCINT30/OC2B/ICP_PD6), S9.1 (OUT)
SENSORE10: IC2.19 (PCINT29/OC1A_PD5), S10.1 (OUT)
SENSORE11: IC2.18 (PCINT28/OC1B_PD4), S11.1 (OUT)
SENSORE12: IC2.40 (PCINT0/ADC0_PA0), S12.1 (OUT)
SENSORE13: IC2.39 (PCINT1/ADC1_PA1), S13.1 (OUT)
SENSORE14: IC2.38 (PCINT2/ADC2_PA2), S14.1 (OUT)
SENSORE15: IC2.37 (PCINT3/ADC3_PA3), S15.1 (OUT)
SENSORE16: IC2.36 (PCINT4/ADC4_PA4), S16.1 (OUT)
SENSORE17: IC2.35 (PCINT5/ADC5_PA5), S17.1 (OUT)
SENSORE18: IC2.34 (PCINT6/ADC6_PA6), S18.1 (OUT)
SENSORE19: IC2.33 (PCINT7/ADC7_PA7), S19.1 (OUT)
SS_644: IC2.5 (PCINT12/OC0B/SS_PB4), IC3.5 (PCINT12/OC0B/SS_PB4)
SS_PIXY: IC3.4 (PCINT11/OC0A/AIN1_PB3), PIXY_CON.7
SW_1: SW1.P$1 (1)
SW_2: SW2.P$1 (1)
TX_0: IC3.14 (PCINT24/RXD0_PD0), JP1.3
TX_BT: IC3.2 (PCINT9/CLKO/T1_PB1), SERIAL_EXTRA.2
TX_LINEE: IC3.16 (PCINT26/INT0_PD2), PL1.13
VMOT: SW_MOTORI.1 (O), VMOT.1

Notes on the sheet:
HOLE
US_connector
Sensori di palla blocco 1
Sensori di palla blocco 2
Sensori di palla blocco 3
Sensori di palla blocco 4
ATmega 644P sensori_palla
Buzzer
Switch
Bussola
Led
CON_motor shield
ATmega 644P
CON_pixy
Supply_Motors
Programmatore AVR 1
Bluetooth
Voltage Regulator
Pin-Header Serial
Jumper

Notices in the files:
parts and their libraries:
cap-pan40: Copyright (C) 2004, Bob Starr
SparkFun-Connectors: Licensing: Creative Commons ShareAlike 4.0 International - https://creativecommons.org/licenses/by-sa/4.0
Wurth_Elektronik_Optoelectronics_rev15b: Copyright: Würth Elektronik
